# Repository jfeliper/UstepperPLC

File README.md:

# UstepperPLC
Adaptación de ustepper para conexión con un PLC
Añadidos a ustepper para usar directamente con un PLC

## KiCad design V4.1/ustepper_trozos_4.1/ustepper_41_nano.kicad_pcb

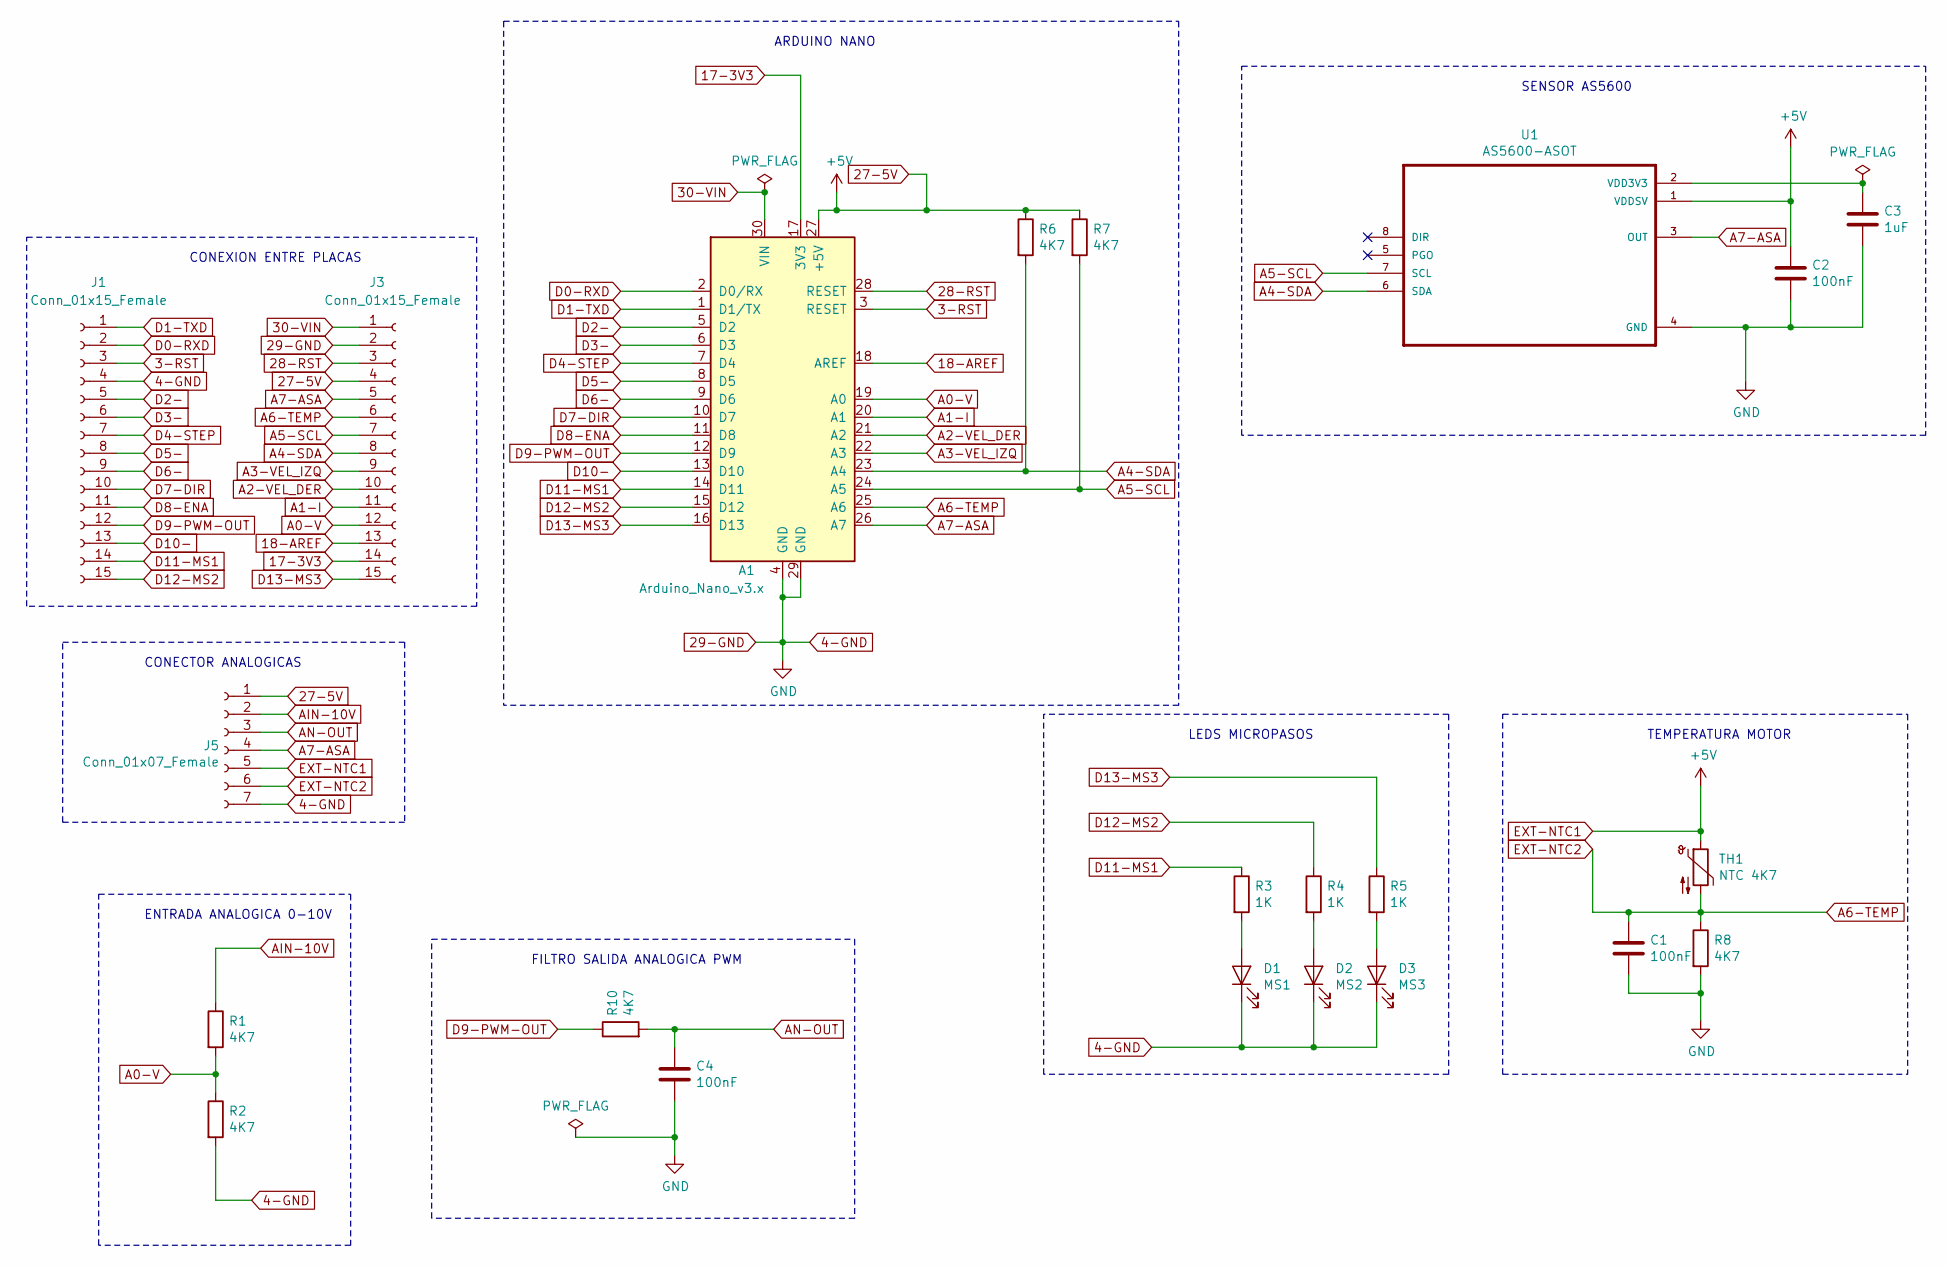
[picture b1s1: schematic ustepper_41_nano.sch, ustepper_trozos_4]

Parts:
A1: Arduino_Nano_v3.x; Arduino_Nano
C1, C2, C4: 100nF; C_1206_3216Metric_Pad1.42x1.75mm_HandSolder
C3: 1uF; C_1206_3216Metric_Pad1.42x1.75mm_HandSolder
D1: MS1; LED_1206_3216Metric_Pad1.42x1.75mm_HandSolder
D2: MS2; LED_1206_3216Metric_Pad1.42x1.75mm_HandSolder
D3: MS3; LED_1206_3216Metric_Pad1.42x1.75mm_HandSolder
J1, J3: Conn_01x15_Female; PinSocket_1x15_P2.54mm_Vertical
J5: Conn_01x07_Female; PinHeader_1x07_P2.54mm_Vertical
R1, R2, R6, R7, R8, R10: 4K7; R_1206_3216Metric_Pad1.42x1.75mm_HandSolder
R3, R4, R5: 1K; R_1206_3216Metric_Pad1.42x1.75mm_HandSolder
TH1: NTC 4K7; R_1206_3216Metric_Pad1.42x1.75mm_HandSolder
U1: AS5600-ASOT; SOIC-8_3.9x4.9mm_P1.27mm

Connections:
3-RST: A1.3 (RESET), J1.3
17-3V3: A1.17 (3V3), J3.14
18-AREF: A1.18 (AREF), J3.13
27-5V: A1.27 (+5V), C2.1, J3.4, J5.1, J5.5, R6.1, R7.1, TH1.1, U1.1 (VDDSV)
28-RST: A1.28 (RESET), J3.3
29-GND: A1.4 (GND), A1.29 (GND), C1.2, C2.2, C3.2, C4.2, D1.1 (K), D2.1 (K), D3.1 (K), J1.4, J3.2, J5.7, R2.2, R8.2, U1.4 (GND)
30-VIN: A1.30 (VIN), J3.1
A0-V: A1.19 (A0), J3.12, R1.2, R2.1
A1-I: A1.20 (A1), J3.11
A2-VEL_DER: A1.21 (A2), J3.10
A3-VEL_IZQ: A1.22 (A3), J3.9
A4-SDA: A1.23 (A4), J3.8, R6.2, U1.6 (SDA)
A5-SCL: A1.24 (A5), J3.7, R7.2, U1.7 (SCL)
A6-TEMP: A1.25 (A6), C1.1, J3.6, J5.6, R8.1, TH1.2
A7-ASA: A1.26 (A7), J3.5, J5.4, U1.3 (OUT)
AIN-10V: J5.2, R1.1
AN-OUT: C4.1, J5.3, R10.2
D0-RXD: A1.2 (D0/RX), J1.2
D1-TXD: A1.1 (D1/TX), J1.1
D2-: A1.5 (D2), J1.5
D3-: A1.6 (D3), J1.6
D4-STEP: A1.7 (D4), J1.7
D5-: A1.8 (D5), J1.8
D6-: A1.9 (D6), J1.9
D7-DIR: A1.10 (D7), J1.10
D8-ENA: A1.11 (D8), J1.11
D9-PWM-OUT: A1.12 (D9), J1.12, R10.1
D10-: A1.13 (D10), J1.13
D11-MS1: A1.14 (D11), J1.14, R3.1
D12-MS2: A1.15 (D12), J1.15, R4.1
D13-MS3: A1.16 (D13), J3.15, R5.1
unnamed: C3.1, U1.2 (VDD3V3)
unnamed: D1.2 (A), R3.2
unnamed: D2.2 (A), R4.2
unnamed: D3.2 (A), R5.2

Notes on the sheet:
SENSOR AS5600
LEDS MICROPASOS
TEMPERATURA MOTOR
ENTRADA ANALOGICA 0-10V
FILTRO SALIDA ANALOGICA PWM
ARDUINO NANO
CONEXION ENTRE PLACAS
CONECTOR ANALOGICAS

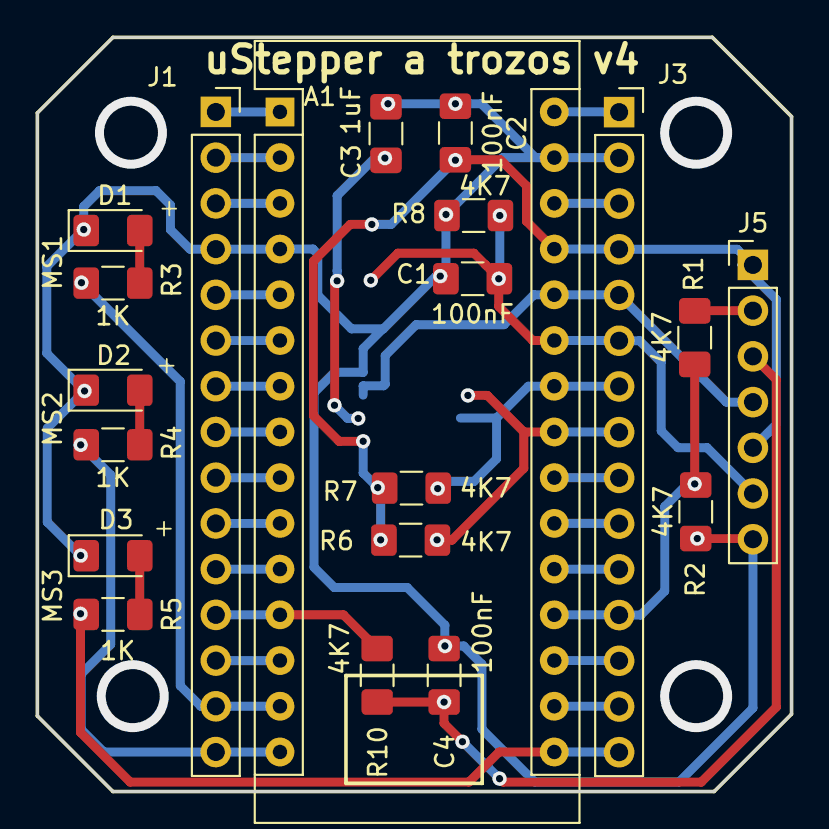
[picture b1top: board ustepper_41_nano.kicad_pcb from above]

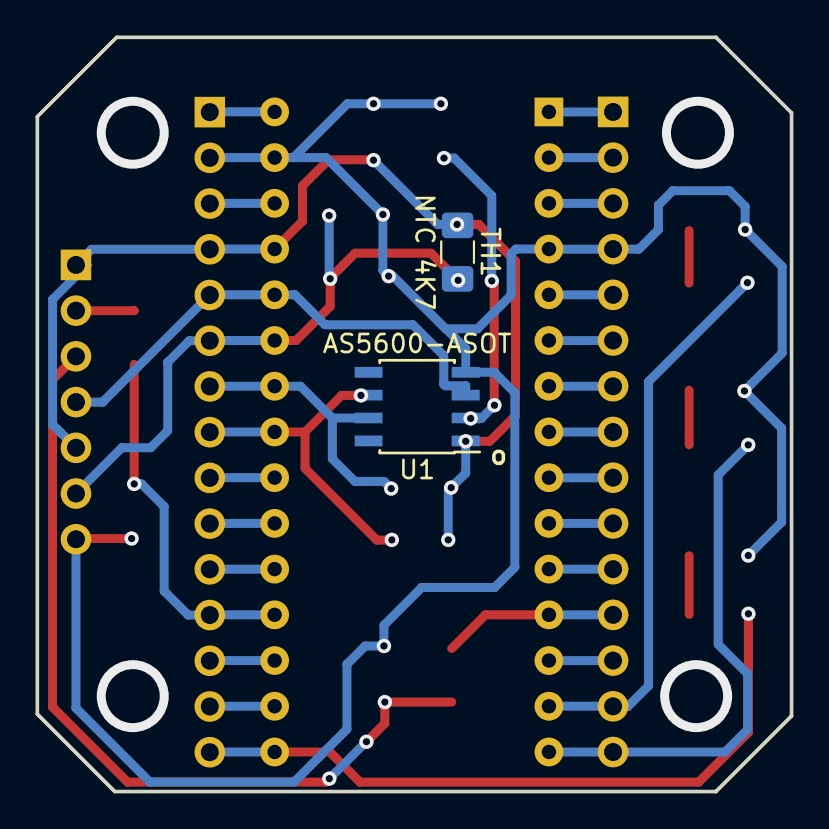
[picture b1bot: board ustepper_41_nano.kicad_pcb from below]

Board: 2 copper layers, 41.9 x 41.9 mm, 22 parts (2 on the bottom side), 35 nets.

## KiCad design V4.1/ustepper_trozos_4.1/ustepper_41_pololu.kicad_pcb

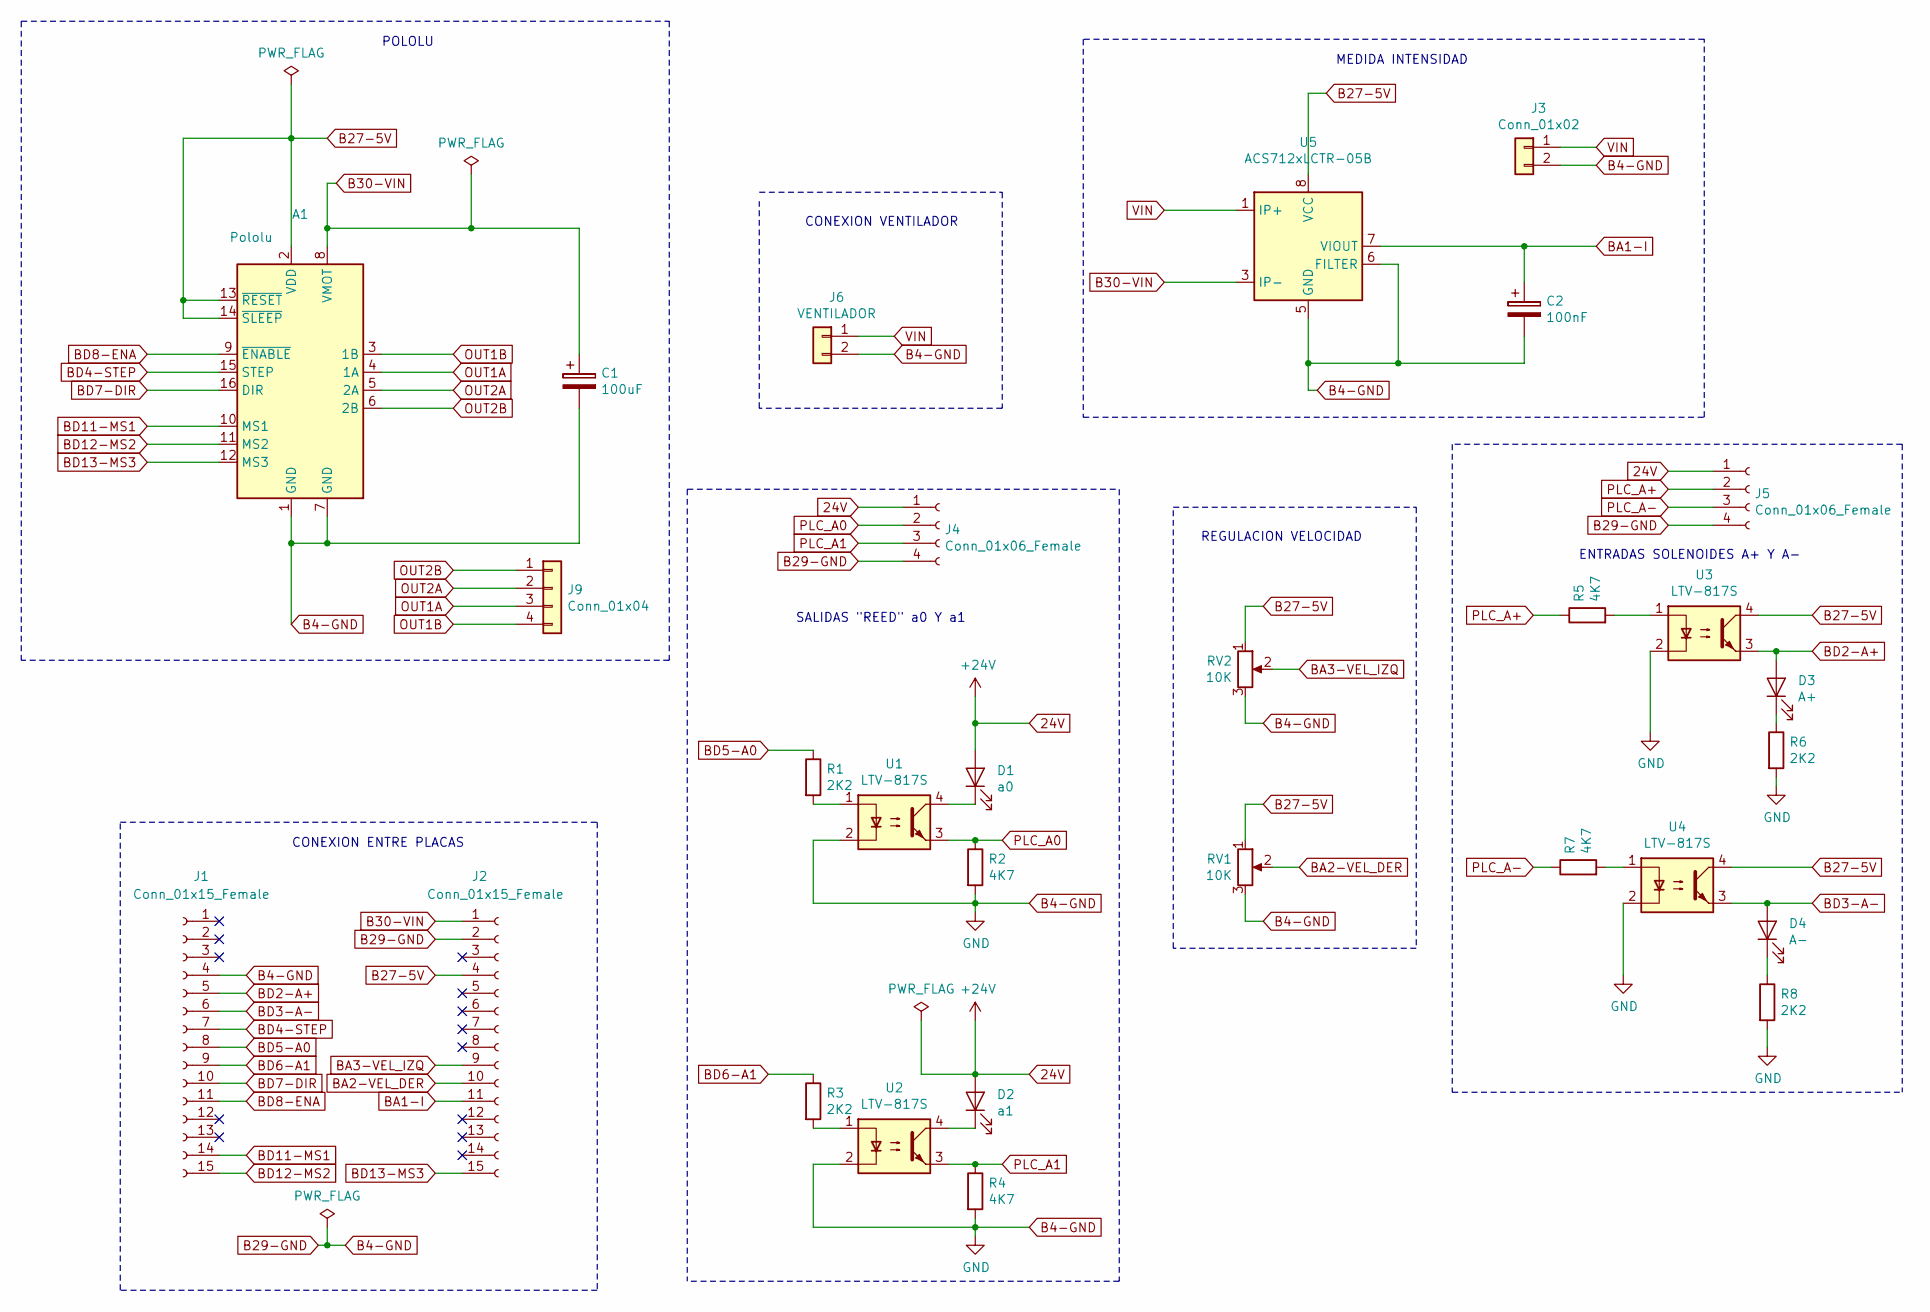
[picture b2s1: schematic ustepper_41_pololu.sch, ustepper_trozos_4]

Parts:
A1: Pololu; Pololu_Breakout-16_15.2x20.3mm
C1: 100uF; CP_Radial_D6.3mm_P2.50mm
C2: 100nF; C_1206_3216Metric_Pad1.42x1.75mm_HandSolder
D1: a0; LED_1206_3216Metric_Pad1.42x1.75mm_HandSolder
D2: a1; LED_1206_3216Metric_Pad1.42x1.75mm_HandSolder
D3: A+; LED_1206_3216Metric_Pad1.42x1.75mm_HandSolder
D4: A-; LED_1206_3216Metric_Pad1.42x1.75mm_HandSolder
J1, J2: Conn_01x15_Female; PinHeader_1x15_P2.54mm_Vertical
J3: Conn_01x02; PhoenixContact_MSTBA_2,5_2-G_1x02_P5.00mm_Horizontal
J4: Conn_01x06_Female; PinSocket_1x04_P2.54mm_Vertical
J5: Conn_01x06_Female; PinHeader_1x04_P2.54mm_Vertical
J6: VENTILADOR; PinHeader_1x02_P2.54mm_Vertical
J9: Conn_01x04; PinHeader_1x04_P2.54mm_Vertical
R1, R3, R6, R8: 2K2; R_1206_3216Metric_Pad1.42x1.75mm_HandSolder
R2, R4, R5, R7: 4K7; R_1206_3216Metric_Pad1.42x1.75mm_HandSolder
RV1, RV2: 10K; PinSocket_1x03_P2.54mm_Vertical
U1, U2, U3, U4: LTV-817S; SMDIP-4_W9.53mm
U5: ACS712xLCTR-05B; SOIC-8_3.9x4.9mm_P1.27mm

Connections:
24V: D1.2 (A), D2.2 (A), J4.1, J5.1
B27-5V: A1.2 (VDD), A1.13 (~RESET), A1.14 (~SLEEP), J2.4, RV1.1, RV2.1, U3.4, U4.4, U5.8 (VCC); also elsewhere on the board
B29-GND: A1.1 (GND), A1.7 (GND), C1.2, C2.2, J1.4, J2.2, J3.2, J4.4, J5.4, J6.2, R2.2, R4.2, R6.2, R8.2, RV1.3, RV2.3, U1.2, U2.2, U3.2, U4.2, U5.5 (GND), U5.6 (FILTER); also elsewhere on the board
B30-VIN: A1.8 (VMOT), C1.1, J2.1, U5.3 (IP-), U5.4 (IP-)
BA1-I: C2.1, J2.11, U5.7 (VIOUT)
BA2-VEL_DER: J2.10, RV1.2; also elsewhere on the board
BA3-VEL_IZQ: J2.9, RV2.2; also elsewhere on the board
BD2-A+: D3.2 (A), J1.5, U3.3
BD3-A-: D4.2 (A), J1.6, U4.3
BD4-STEP: A1.15 (STEP), J1.7
BD5-A0: J1.8, R1.1
BD6-A1: J1.9, R3.1
BD7-DIR: A1.16 (DIR), J1.10
BD8-ENA: A1.9 (~ENABLE), J1.11
BD11-MS1: A1.10 (MS1), J1.14
BD12-MS2: A1.11 (MS2), J1.15
BD13-MS3: A1.12 (MS3), J2.15
unnamed: D1.1 (K), U1.4
unnamed: D2.1 (K), U2.4
unnamed: D3.1 (K), R6.1
unnamed: D4.1 (K), R8.1
unnamed: R1.2, U1.1
unnamed: R3.2, U2.1
unnamed: R5.2, U3.1
unnamed: R7.2, U4.1
OUT1A: A1.4 (1A), J9.3
OUT1B: A1.3 (1B), J9.4
OUT2A: A1.5 (2A), J9.2
OUT2B: A1.6 (2B), J9.1
PLC_A0: J4.2, R2.1, U1.3
PLC_A1: J4.3, R4.1, U2.3
PLC_A+: J5.2, R5.1
PLC_A-: J5.3, R7.1
VIN: J3.1, J6.1, U5.1 (IP+), U5.2 (IP+)

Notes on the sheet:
SALIDAS "REED" a0 Y a1
ENTRADAS SOLENOIDES A+ Y A-
MEDIDA INTENSIDAD
POLOLU
CONEXION ENTRE PLACAS
CONEXION VENTILADOR
REGULACION VELOCIDAD

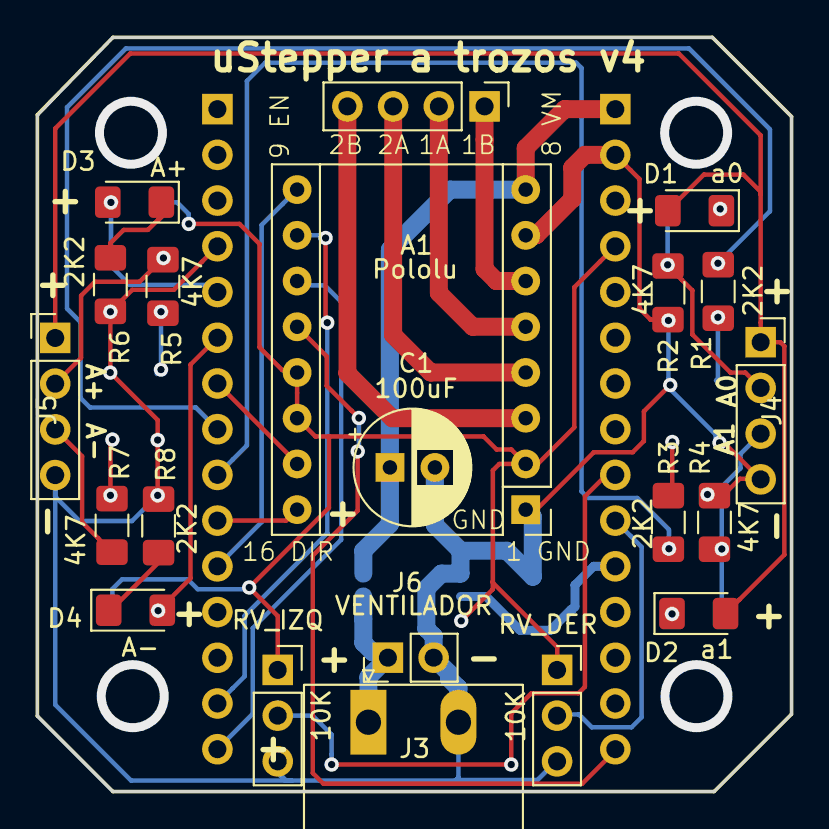
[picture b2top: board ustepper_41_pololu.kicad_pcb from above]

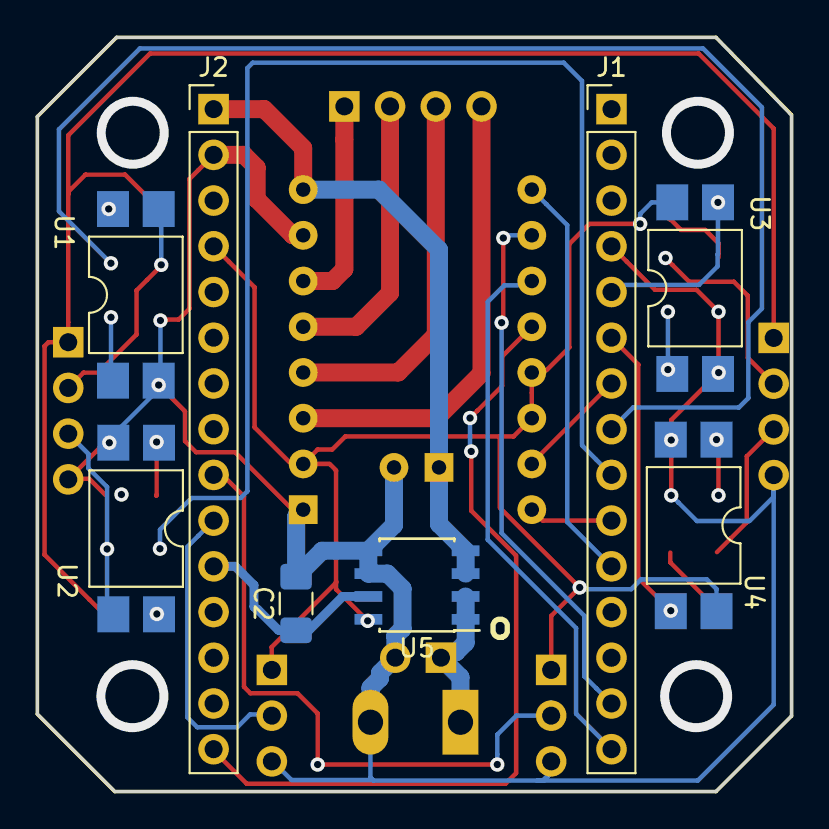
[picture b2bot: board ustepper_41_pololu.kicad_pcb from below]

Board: 2 copper layers, 41.9 x 41.9 mm, 29 parts (8 on the bottom side), 34 nets.

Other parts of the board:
RV_DER: 10K; PinSocket_1x03_P2.54mm_Vertical
RV_IZQ: 10K; PinSocket_1x03_P2.54mm_Vertical

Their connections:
B27-5V: RV_DER.1, RV_IZQ.1; also elsewhere on the board
B29-GND: RV_DER.3, RV_IZQ.3; also elsewhere on the board
BA2-VEL_DER: RV_DER.2; also elsewhere on the board
BA3-VEL_IZQ: RV_IZQ.2; also elsewhere on the board

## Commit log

2019-01-19 Create Lista de deseos
2019-01-24 Update Lista de deseos
2019-01-26 Update Lista de deseos
    Hola Joaquín, este archivo lo he editado sobre el tuyo directamente on-line, ahora voy a intentar suscribirme y hacer algo desde mi cuenta.
2019-01-26 Create uStepperServo.ino
    Ejemplo de control de servo de la librería ustepper
2019-01-26 Add files via upload
    Esquema original de la placa ustepper
2019-01-27 Propuesta de esquema y placas para V4 ustepperPLC
2019-01-27 Cambio de nombre de las imagenes 3D ustepperPLC
2019-01-27 Añadido un pdf con las vistas 3D de las dos placas, desde arriba y desde abajo
2019-01-28 Placas compltadas. Pendiente de revisar
2019-01-29 Versión 4.1 con entradas y salidas a PLC, y potenciometros para velocidad
2019-01-29 Borro la versión 4
